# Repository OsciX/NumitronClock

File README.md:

# NumitronClock
Code repository for my Numitron Clock project.
Requires t3db0t's button library, located at https://github.com/t3db0t/Button, and Adafruit's RTClib from https://github.com/adafruit/RTClib.

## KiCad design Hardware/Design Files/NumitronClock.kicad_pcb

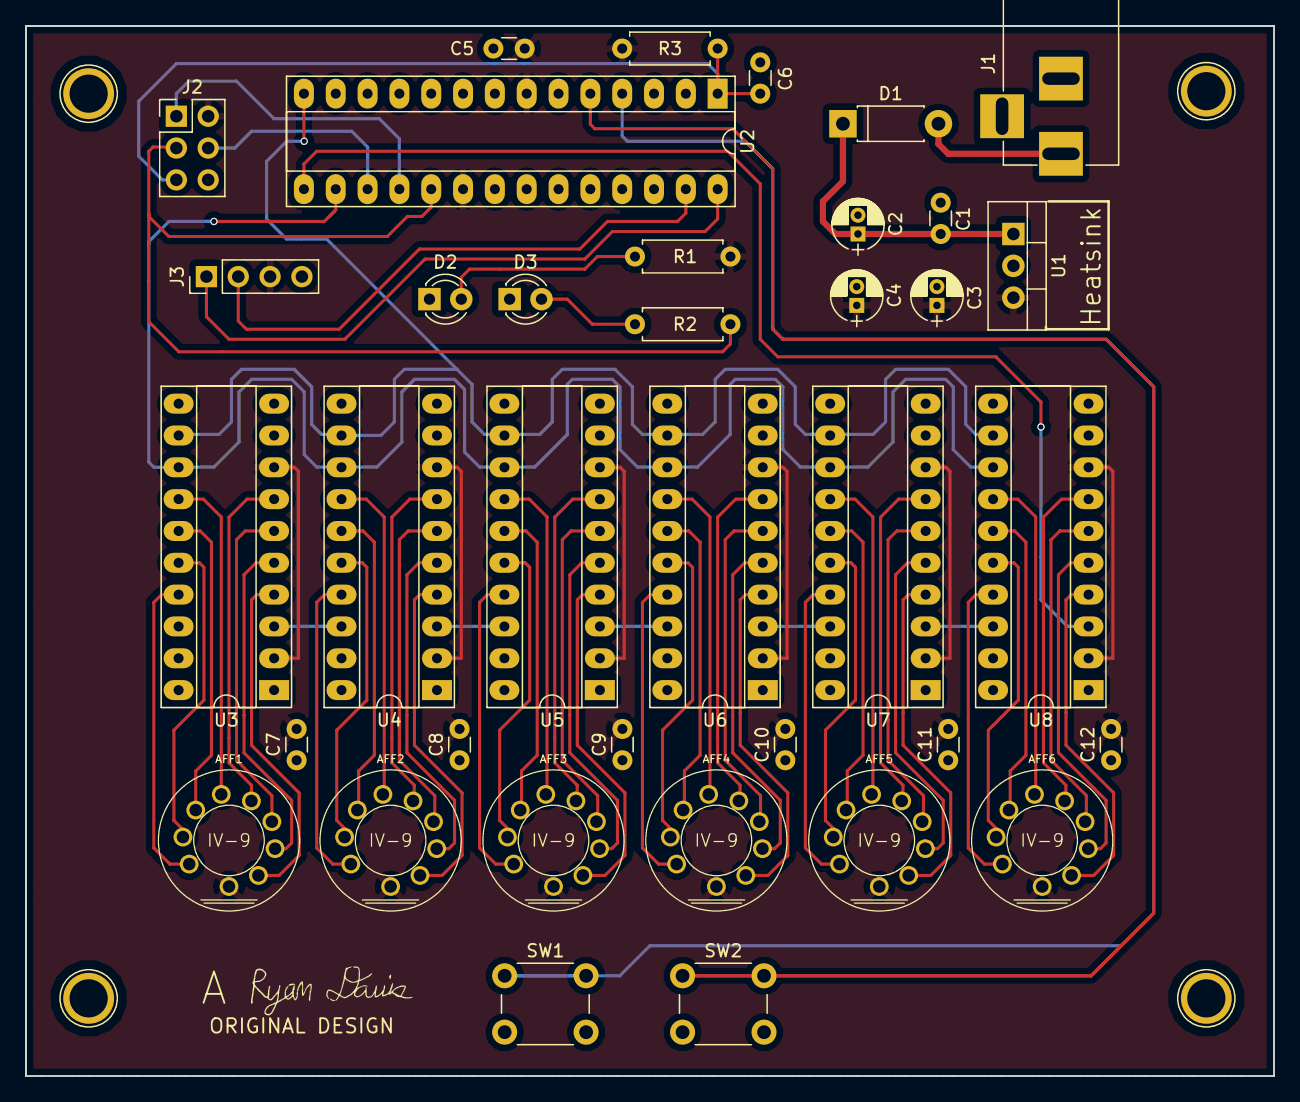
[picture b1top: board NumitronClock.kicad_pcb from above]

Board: 2 copper layers, 99.6 x 83.8 mm, 37 parts (0 on the bottom side), 70 nets.

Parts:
AFF1, AFF2, AFF3, AFF4, AFF5, AFF6: Numitron_IV9; NUM_IV-9
C1, C5, C7, C8, C9, C10, C11, C12: 0.1uf; C_Disc_D3.0mm_W1.6mm_P2.50mm
C2, C4: 10uf; CP_Radial_D4.0mm_P1.50mm
C3: 100uf; CP_Radial_D4.0mm_P1.50mm
C6: 0.01uf; C_Disc_D3.0mm_W1.6mm_P2.50mm
D1: 1N4001; D_DO-41_SOD81_P7.62mm_Horizontal
D2, D3: LED; LED_D3.0mm
J1: BARREL_JACK
J2: ISP; Pin_Header_Straight_2x03_Pitch2.54mm
J3: RTC_Breakout; Pin_Header_Straight_1x04_Pitch2.54mm
R1, R2: 1k; R_Axial_DIN0207_L6.3mm_D2.5mm_P7.62mm_Horizontal
R3: 10k; R_Axial_DIN0207_L6.3mm_D2.5mm_P7.62mm_Horizontal
SW1, SW2: TACT_BUTTON; SW_PUSH_6mm
U1: 7805; TO-220_Vertical
U2: ATMEGA328-PU; DIP-28_W7.62mm_Socket_LongPads
U3, U4, U5, U6, U7, U8: TPIC6B595; DIP-20_W7.62mm_Socket_LongPads

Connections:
+5V: AFF1.1, AFF2.1, AFF3.1, AFF4.1, AFF5.1, AFF6.1, C3.1, C4.1, C5.1, C7.2, C8.2, C9.2, C10.2, C11.2, C12.2, J2.2, J3.3, R1.2, R3.2, U1.3, U2.7, U2.20, U3.2, U3.8, U4.2, U4.8, U5.2, U5.8, U6.2, U6.8, U7.2, U7.8, U8.2, U8.8
/Display/RCK: U2.14, U3.12, U4.12, U5.12, U6.12, U7.12, U8.12
/Display/SERIN: U2.15, U8.3
/Display/SRCK: U2.16, U3.13, U4.13, U5.13, U6.13, U7.13, U8.13
/MISO: J2.1, U2.18
/MODE: SW1.1, U2.4
/MOSI: J2.4, U2.17
/RST: C6.1, J2.5, R3.1, U2.1
/SCK: J2.3, R2.2, U2.19
/SET: SW2.1, U2.5
GND: C1.2, C2.2, C3.2, C4.2, C5.2, C6.2, C7.1, C8.1, C9.1, C10.1, C11.1, C12.1, D2.1, D3.1, J1.2, J1.3, J2.6, J3.4, SW1.2, SW2.2, U1.2, U2.8, U2.22, U3.9, U3.10, U3.11, U3.19, U4.9, U4.10, U4.11, U4.19, U5.9, U5.10, U5.11, U5.19, U6.9, U6.10, U6.11, U6.19, U7.9, U7.10, U7.11, U7.19, U8.9, U8.10, U8.11, U8.19
unnamed: AFF1.2, U3.4
unnamed: AFF1.3, U3.5
unnamed: AFF1.4, U3.6
unnamed: AFF1.5, U3.7
unnamed: AFF1.6, U3.14
unnamed: AFF1.7, U3.15
unnamed: AFF1.8, U3.16
unnamed: AFF1.9, U3.17
unnamed: AFF2.2, U4.4
unnamed: AFF2.3, U4.5
unnamed: AFF2.4, U4.6
unnamed: AFF2.5, U4.7
unnamed: AFF2.6, U4.14
unnamed: AFF2.7, U4.15
unnamed: AFF2.8, U4.16
unnamed: AFF2.9, U4.17
unnamed: AFF3.2, U5.4
unnamed: AFF3.3, U5.5
unnamed: AFF3.4, U5.6
unnamed: AFF3.5, U5.7
unnamed: AFF3.6, U5.14
unnamed: AFF3.7, U5.15
unnamed: AFF3.8, U5.16
unnamed: AFF3.9, U5.17
unnamed: AFF4.2, U6.4
unnamed: AFF4.3, U6.5
unnamed: AFF4.4, U6.6
unnamed: AFF4.5, U6.7
unnamed: AFF4.6, U6.14
unnamed: AFF4.7, U6.15
unnamed: AFF4.8, U6.16
unnamed: AFF4.9, U6.17
unnamed: AFF5.2, U7.4
unnamed: AFF5.3, U7.5
unnamed: AFF5.4, U7.6
unnamed: AFF5.5, U7.7
unnamed: AFF5.6, U7.14
unnamed: AFF5.7, U7.15
unnamed: AFF5.8, U7.16
unnamed: AFF5.9, U7.17
unnamed: AFF6.2, U8.4
unnamed: AFF6.3, U8.5
unnamed: AFF6.4, U8.6
unnamed: AFF6.5, U8.7
unnamed: AFF6.6, U8.14
unnamed: AFF6.7, U8.15
unnamed: AFF6.8, U8.16
unnamed: AFF6.9, U8.17
unnamed: D1.2, J1.1
unnamed: D2.2, R1.1
unnamed: D3.2, R2.1
unnamed: J3.1, U2.28
unnamed: J3.2, U2.27
unnamed: U3.3, U4.18
unnamed: U4.3, U5.18
unnamed: U5.3, U6.18
unnamed: U6.3, U7.18
unnamed: U7.3, U8.18
VCC: C1.1, C2.1, D1.1, U1.1

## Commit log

2017-04-10 Add working code
    Add .ino files for Arduino code, and update README to include
    dependencies.
2017-10-06 Add circuit board design files
2019-01-15 Add images
    Add images for presentation and documentation purposes
